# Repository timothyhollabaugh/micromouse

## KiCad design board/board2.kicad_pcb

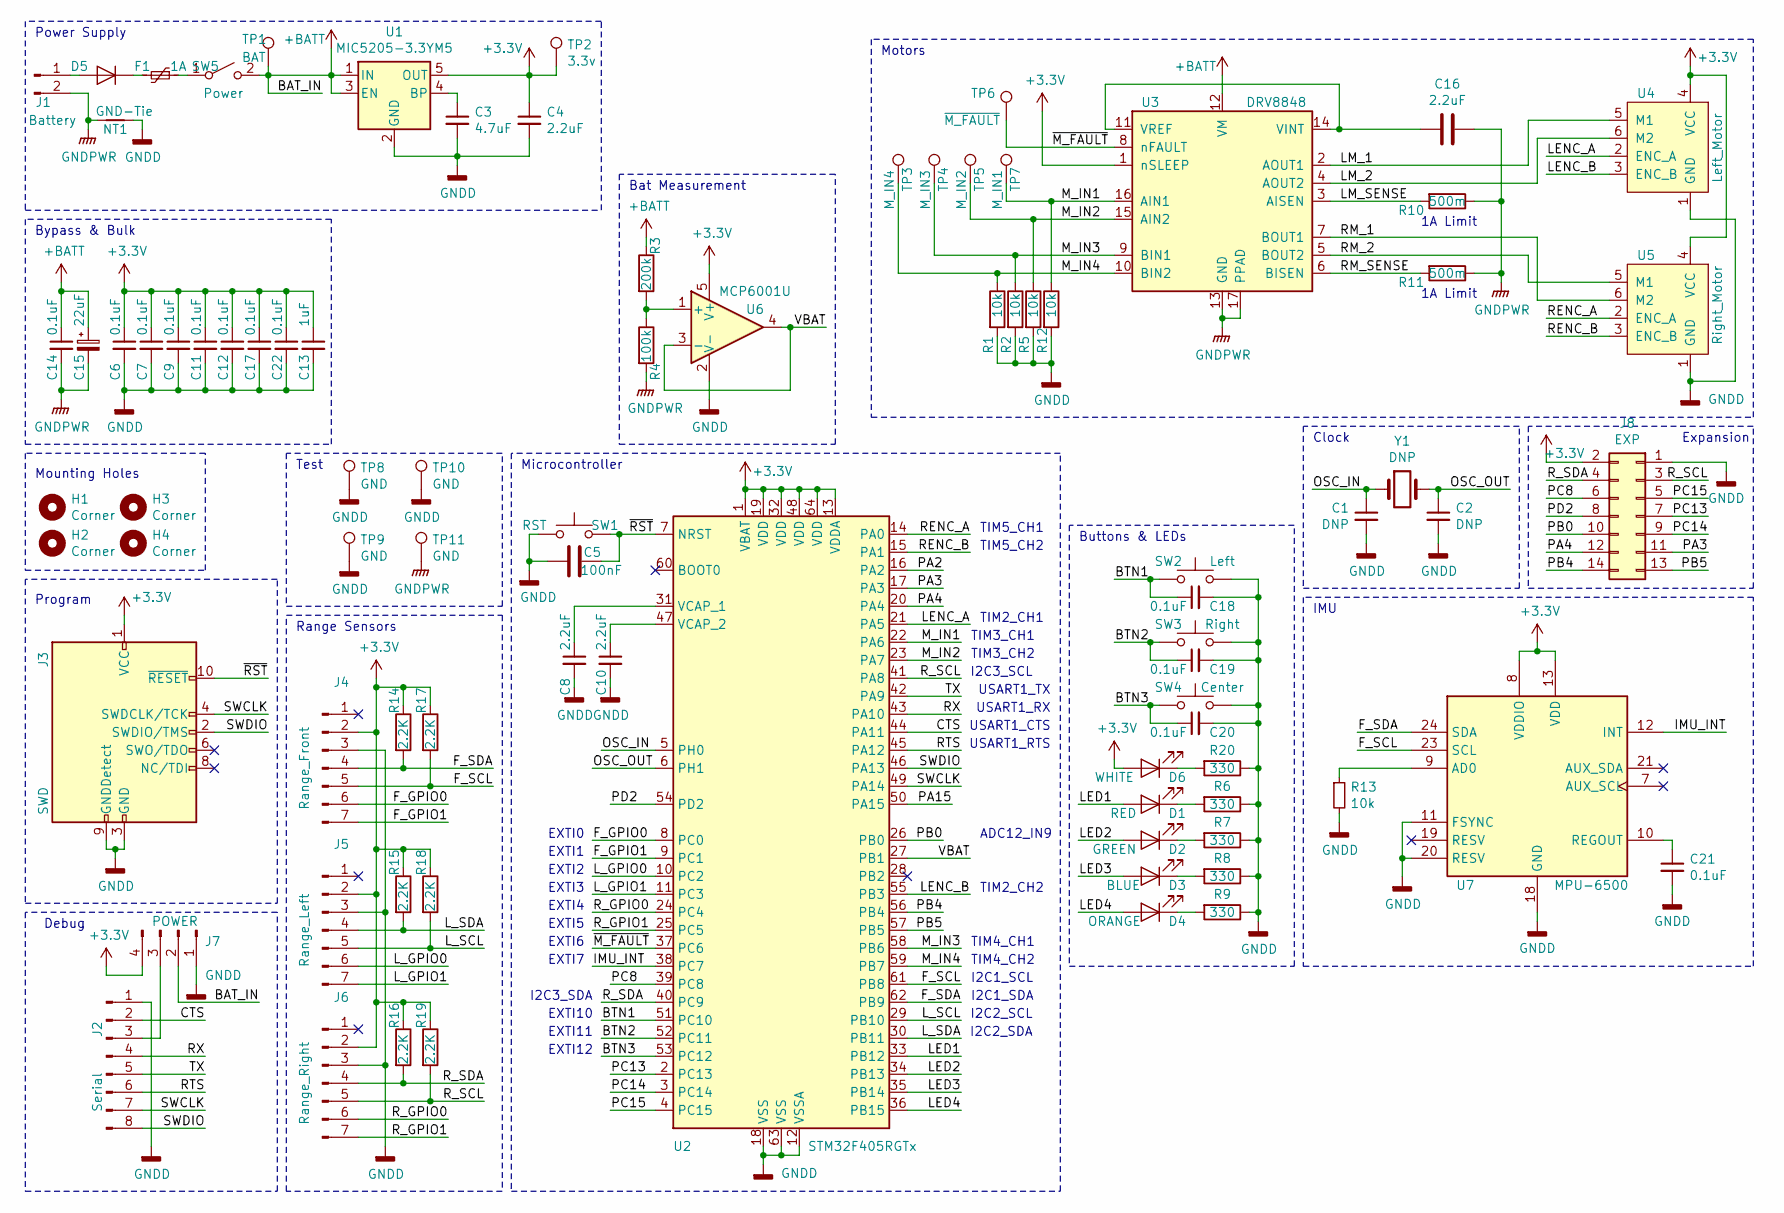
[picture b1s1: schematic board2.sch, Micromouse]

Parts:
C1, C2: DNP; C_0603_1608Metric
C3: 4.7uF; C_0603_1608Metric
C4, C8, C10, C16: 2.2uF; C_0603_1608Metric
C5: 100nF; C_0603_1608Metric
C6, C7, C9, C11, C12, C14, C17, C18, C19, C20, C21, C22: 0.1uF; C_0603_1608Metric
C13: 1uF; C_0603_1608Metric
C15: 22uF; CP_Elec_4x4.5
D1: RED; LED_0603_1608Metric
D2: GREEN; LED_0603_1608Metric
D3: BLUE; LED_0603_1608Metric
D4: ORANGE; LED_0603_1608Metric
D5: DB2441700L; SC-110A-2
D6: WHITE; LED_0603_1608Metric
F1: 1A; Littlefuse_154
H1, H2, H3, H4: Corner; MountingHole_2.2mm_M2
J1: Battery; PinHeader_1x02_P2.54mm_Horizontal
J2: Serial; PinHeader_1x08_P2.54mm_Vertical_SMD_Pin1Left
J3: SWD; PinHeader_2x05_P1.27mm_Vertical_SMD
J4: Range_Front; PinSocket_1x07_P2.54mm_Vertical
J5: Range_Left; PinSocket_1x07_P2.54mm_Vertical
J6: Range_Right; PinSocket_1x07_P2.54mm_Vertical
J7: POWER; PinHeader_1x04_P2.54mm_Vertical_SMD_Pin1Left
J8: EXP; PinHeader_2x07_P2.00mm_Vertical_SMD
NT1: GND-Tie; NetTie-2_SMD_Pad0.5mm
R1, R2, R5, R12, R13: 10k; R_0603_1608Metric
R3: 200k; R_0603_1608Metric
R4: 100k; R_0603_1608Metric
R6, R7, R8, R9, R20: 330; R_0603_1608Metric
R10, R11: 500m; R_1210_3225Metric
R14, R15, R16, R17, R18, R19: 2.2K; R_0603_1608Metric
SW1: RST; SW_SPST_PTS810
SW2: Left; SW_SPST_PTS810
SW3: Right; SW_SPST_PTS810
SW4: Center; SW_SPST_PTS810
SW5: Power; PinHeader_2x01_P2.54mm_Vertical_SMD
TP1: BAT; TestPoint_Pad_1.8x1.0mm
TP2: 3.3v; TestPoint_Pad_1.8x1.0mm
TP3: M_IN4; TestPoint_Pad_1.8x1.0mm
TP4: M_IN3; TestPoint_Pad_1.8x1.0mm
TP5: M_IN2; TestPoint_Pad_1.8x1.0mm
TP6: ~M_FAULT; TestPoint_Pad_1.8x1.0mm
TP7: M_IN1; TestPoint_Pad_1.8x1.0mm
TP8, TP9, TP10, TP11: GND; TestPoint_Pad_1.8x1.0mm
U1: MIC5205-3.3YM5; SOT-23-5
U2: STM32F405RGTx; LQFP-64_10x10mm_P0.5mm
U3: DRV8848; TSSOP-16_4.4x5mm_P0.65mm
U4: Left_Motor; Molex_PicoBlade_53261-0671_1x06-1MP_P1.25mm_Horizontal
U5: Right_Motor; Molex_PicoBlade_53261-0671_1x06-1MP_P1.25mm_Horizontal
U6: MCP6001U; SOT-23-5
U7: MPU-6500; InvenSense_QFN-24_4x4mm_P0.5mm
Y1: DNP; Crystal_SMD_0603-2Pin_6.0x3.5mm

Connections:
+3V3: C4.1, C6.1, C7.1, C9.1, C11.1, C12.1, C13.1, C17.1, C22.1, D6.2 (A), J3.1 (VCC), J4.2, J5.2, J6.2, J7.4, J8.2, R14.1, R15.1, R16.1, R17.1, R18.1, R19.1, TP2.1, U1.5 (OUT), U2.1 (VBAT), U2.13 (VDDA), U2.19 (VDD), U2.32 (VDD), U2.48 (VDD), U2.64 (VDD), U3.1 (nSLEEP), U4.4 (VCC), U5.4 (VCC), U6.5 (V+), U7.8 (VDDIO), U7.13 (VDD)
+BATT: C14.1, C15.1, J7.2, R3.1, SW5.2 (B), TP1.1, U1.1 (IN), U1.3 (EN), U3.12 (VM)
/BTN1: C18.1, SW2.1, U2.51 (PC10)
/BTN2: C19.1, SW3.1, U2.52 (PC11)
/BTN3: C20.1, SW4.1, U2.53 (PC12)
/CTS: J2.2, U2.44 (PA11)
/F_GPIO0: J4.6, U2.8 (PC0)
/F_GPIO1: J4.7, U2.9 (PC1)
/F_SCL: J4.5, R17.2, U2.61 (PB8), U7.23 (SCL)
/F_SDA: J4.4, R14.2, U2.62 (PB9), U7.24 (SDA)
/IMU_INT: U2.38 (PC7), U7.12 (INT)
/LED1: D1.2 (A), U2.33 (PB12)
/LED2: D2.2 (A), U2.34 (PB13)
/LED3: D3.2 (A), U2.35 (PB14)
/LED4: D4.2 (A), U2.36 (PB15)
/LENC_A: U2.21 (PA5), U4.2 (ENC_A)
/LENC_B: U2.55 (PB3), U4.3 (ENC_B)
/LM_1: U3.2 (AOUT1), U4.5 (M1)
/LM_2: U3.4 (AOUT2), U4.6 (M2)
/LM_SENSE: R10.2, U3.3 (AISEN)
/L_GPIO0: J5.6, U2.10 (PC2)
/L_GPIO1: J5.7, U2.11 (PC3)
/L_SCL: J5.5, R18.2, U2.29 (PB10)
/L_SDA: J5.4, R15.2, U2.30 (PB11)
/M_IN1: R12.1, TP7.1, U2.22 (PA6), U3.16 (AIN1)
/M_IN2: R5.1, TP5.1, U2.23 (PA7), U3.15 (AIN2)
/M_IN3: R2.1, TP4.1, U2.58 (PB6), U3.9 (BIN1)
/M_IN4: R1.1, TP3.1, U2.59 (PB7), U3.10 (BIN2)
/OSC_IN: C1.1, U2.5 (PH0), Y1.1
/OSC_OUT: C2.1, U2.6 (PH1), Y1.2
/PA3: J8.11, U2.17 (PA3)
/PA4: J8.12, U2.20 (PA4)
/PB0: J8.10, U2.26 (PB0)
/PB4: J8.14, U2.56 (PB4)
/PB5: J8.13, U2.57 (PB5)
/PC8: J8.6, U2.39 (PC8)
/PC13: J8.7, U2.2 (PC13)
/PC14: J8.9, U2.3 (PC14)
/PC15: J8.5, U2.4 (PC15)
/PD2: J8.8, U2.54 (PD2)
/RENC_A: U2.14 (PA0), U5.2 (ENC_A)
/RENC_B: U2.15 (PA1), U5.3 (ENC_B)
/RM_1: U3.7 (BOUT1), U5.6 (M2)
/RM_2: U3.5 (BOUT2), U5.5 (M1)
/RM_SENSE: R11.2, U3.6 (BISEN)
/RTS: J2.6, U2.45 (PA12)
/RX: J2.4, U2.43 (PA10)
/R_GPIO0: J6.6, U2.24 (PC4)
/R_GPIO1: J6.7, U2.25 (PC5)
/R_SCL: J6.5, J8.3, R19.2, U2.41 (PA8)
/R_SDA: J6.4, J8.4, R16.2, U2.40 (PC9)
/SWCLK: J2.7, J3.4 (SWDCLK/TCK), U2.49 (PA14)
/SWDIO: J2.8, J3.2 (SWDIO/TMS), U2.46 (PA13)
/TX: J2.5, U2.42 (PA9)
/VBAT: U2.27 (PB1), U6.3 (-), U6.4
/~M_FAULT: TP6.1, U2.37 (PC6), U3.8 (nFAULT)
/~RST: C5.1, J3.10 (~RESET~), SW1.2, U2.7 (NRST)
GNDD: C1.2, C2.2, C3.2, C4.2, C5.2, C6.2, C7.2, C8.2, C9.2, C10.2, C11.2, C12.2, C13.2, C17.2, C18.2, C19.2, C20.2, C21.2, C22.2, J2.1, J3.3 (GND), J3.5 (GND), J3.9 (GNDDetect), J4.3, J5.3, J6.3, J7.1, J8.1, NT1.2, R1.2, R2.2, R5.2, R6.1, R7.1, R8.1, R9.1, R12.2, R13.2, R20.1, SW1.1, SW2.2, SW3.2, SW4.2, TP8.1, TP9.1, TP10.1, U1.2 (GND), U2.12 (VSSA), U2.18 (VSS), U2.63 (VSS), U4.1 (GND), U5.1 (GND), U6.2 (V-), U7.11 (FSYNC), U7.18 (GND), U7.20 (RESV)
GNDPWR: C14.2, C15.2, C16.1, J1.2, NT1.1, R4.2, R10.1, R11.1, TP11.1, U3.13 (GND), U3.17 (PPAD)
unnamed: C3.1, U1.4 (BP)
unnamed: C8.1, U2.31 (VCAP_1)
unnamed: C10.1, U2.47 (VCAP_2)
unnamed: C16.2, U3.11 (VREF), U3.14 (VINT)
unnamed: C21.1, U7.10 (REGOUT)
unnamed: D1.1 (K), R6.2
unnamed: D2.1 (K), R7.2
unnamed: D3.1 (K), R8.2
unnamed: D4.1 (K), R9.2
unnamed: D5.1 (K), F1.2
unnamed: D5.2 (A), J1.1
unnamed: D6.1 (K), R20.2
unnamed: F1.1, SW5.1 (A)
unnamed: J2.3, J7.3
unnamed: R3.2, R4.1, U6.1 (+)
unnamed: R13.1, U7.9 (AD0)

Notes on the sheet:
TIM3_CH1
TIM3_CH2
TIM4_CH1
TIM4_CH2
TIM5_CH1
TIM5_CH2
TIM2_CH1
TIM2_CH2
I2C1_SCL
I2C1_SDA
I2C2_SCL
I2C2_SDA
I2C3_SCL
I2C3_SDA
EXTI0
EXTI1
EXTI2
EXTI3
EXTI4
EXTI5
EXTI6
USART1_TX
USART1_RX
USART1_CTS
USART1_RTS
EXTI10
EXTI11
EXTI12
ADC12_IN9
EXTI7
Range Sensors
IMU
Microcontroller
Buttons & LEDs
Expansion
Clock
Program
Debug
Test
Power Supply

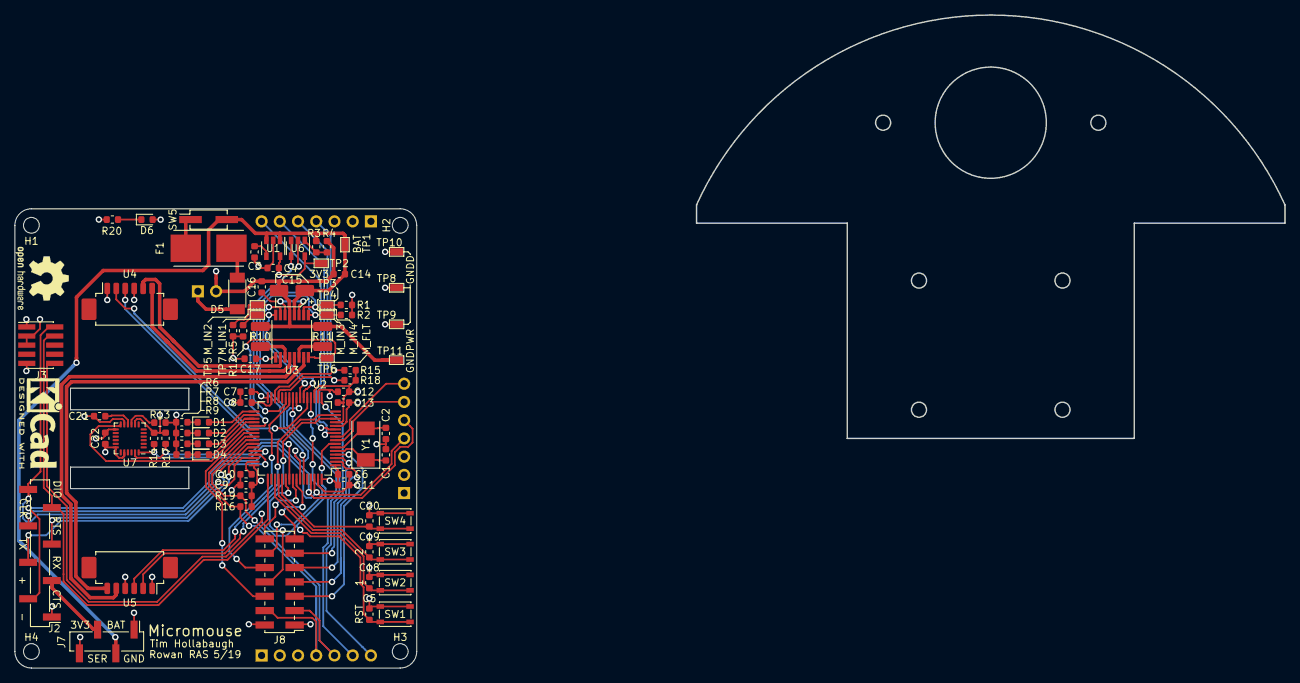
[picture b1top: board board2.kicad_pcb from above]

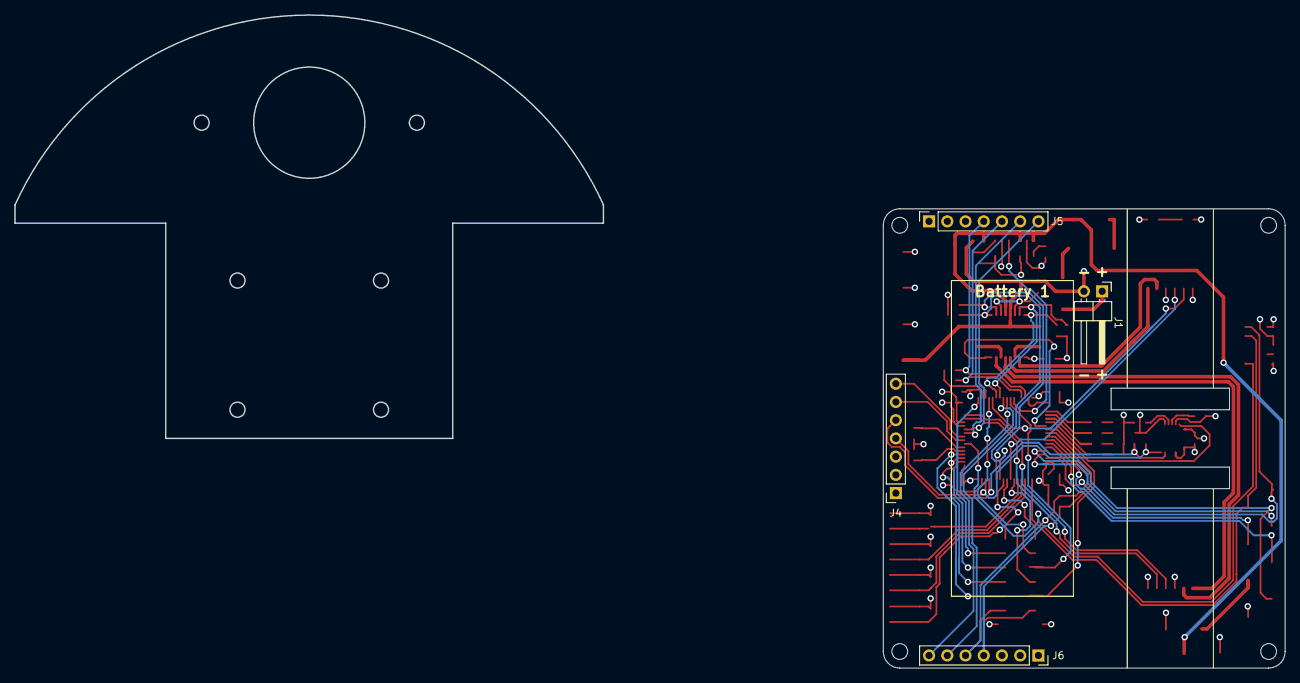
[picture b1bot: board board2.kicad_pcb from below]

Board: 4 copper layers, 177.0 x 91.0 mm, 86 parts (4 on the bottom side), 75 nets.

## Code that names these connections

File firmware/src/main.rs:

#![no_std]
#![no_main]

/**
 *
 * Important mechanical parameters:
 *
 *  - wheel diameter: 32mm
 *  - wheel circumference: 100mm
 *  - gear raitio: 75:1
 *  - counts per motor rev: 12
 *  - counts per wheel rev: 900
 *  - counts per mm: 9
 *  - wheelbase diameter: 73mm
 *  - wheelbase circumference: 229.336mm
 *  - ticks per spin: 2064.03
 *
 *  Positive spin is clockwise (right)
 *  Positive linear is forward
 *
 */
// pick a panicking behavior
// you can put a breakpoint on `rust_begin_unwind` to catch panics
extern crate panic_halt;

pub mod battery;
pub mod motors;
pub mod time;
pub mod uart;
pub mod vl6180x;

use core::fmt::Write;
use cortex_m_rt::entry;
use cortex_m_rt::exception;
use cortex_m_rt::ExceptionFrame;
use stm32f4xx_hal as stm32f4;
use stm32f4xx_hal::prelude::*;
use stm32f4xx_hal::stm32 as stm32f405;

use serde::Serialize;

use heapless::Vec;

use postcard;

use typenum::consts::U1024;

use mouse::comms::DebugMsg;
use mouse::comms::DebugPacket;
#[allow(unused_imports)]
use mouse::config::*;
use mouse::map::Direction;
use mouse::map::Orientation;
use mouse::map::Vector;
use mouse::mouse::Mouse;
use mouse::mouse::MouseConfig;
use mouse::mouse::MouseDebug;

use crate::battery::Battery;
use crate::time::Time;

use crate::uart::Uart;

use crate::motors::{Encoder, Motor};

use crate::motors::left::{LeftEncoder, LeftMotor};
use crate::motors::right::{RightEncoder, RightMotor};

// Setup the master clock out
pub fn mco2_setup(rcc: &stm32f405::RCC, gpioc: &stm32f405::GPIOC) {
    rcc.ahb1enr.write(|w| w.gpiocen().set_bit());
    rcc.cfgr.modify(|_, w| w.mco2().sysclk());
    gpioc.moder.write(|w| w.moder9().alternate());
    gpioc.afrh.write(|w| w.afrh9().af0());
}

#[entry]
fn main() -> ! {
    let p = stm32f4::stm32::Peripherals::take().unwrap();
    let _cp = stm32f405::CorePeripherals::take().unwrap();

    // Init non-hal things
    let mut time = Time::setup(&p.RCC, p.TIM1);

    while time.now() < 10000 {}

    let mut battery = Battery::setup(&p.RCC, &p.GPIOB, p.ADC1);

    let mut uart = Uart::setup(&p.RCC, p.USART1, &p.GPIOA);

    let mut left_motor = LeftMotor::setup(&p.RCC, p.TIM3, &p.GPIOA);
    let left_encoder = LeftEncoder::setup(&p.RCC, &p.GPIOA, &p.GPIOB, p.TIM2);

    let mut right_motor = RightMotor::setup(&p.RCC, p.TIM4, &p.GPIOB);
    let right_encoder = RightEncoder::setup(&p.RCC, &p.GPIOA, p.TIM5);

    // Init the hal things
    let rcc = p.RCC.constrain();
    let clocks = rcc.cfgr.freeze();

    let gpioa = p.GPIOA.split();
    let gpiob = p.GPIOB.split();
    let gpioc = p.GPIOC.split();

    let mut red_led = gpiob.pb12.into_push_pull_output();
    let mut green_led = gpiob.pb13.into_push_pull_output();
    let mut blue_led = gpiob.pb14.into_push_pull_output();
    let mut orange_led = gpiob.pb15.into_push_pull_output();

    let left_button = gpioc.pc10.into_pull_up_input();
    let _middle_button = gpioc.pc11.into_pull_up_input();
    let right_button = gpioc.pc12.into_pull_up_input();

    orange_led.set_high().ok();
    blue_led.set_low().ok();

    uart.add_bytes(b"Initializing\n").ok();

    let mut front_distance = {
        let scl = gpiob.pb8.into_open_drain_output().into_alternate_af4();
        let sda = gpiob.pb9.into_open_drain_output().into_alternate_af4();

        let mut gpio0 = gpioc.pc0.into_open_drain_output();
        gpio0.set_high().ok();

        let mut gpio1 = gpioc.pc1.into_open_drain_output();
        gpio1.set_high().ok();

        let i2c =
            stm32f4::i2c::I2c::i2c1(p.I2C1, (scl, sda), 100.khz(), clocks);

        time.delay(10000);

        let mut distance = vl6180x::VL6180x::new(i2c, 0x29);
        distance.init_private_registers();
        distance.init_default();
        distance
    };

    orange_led.set_low().ok();
    blue_led.set_high().ok();

    let mut left_distance = {
        let scl = gpiob.pb10.into_open_drain_output().into_alternate_af4();
        let sda = gpiob.pb11.into_open_drain_output().into_alternate_af4();

        let mut gpio0 = gpioc.pc2.into_open_drain_output();
        gpio0.set_high().ok();

        let mut gpio1 = gpioc.pc3.into_open_drain_output();
        gpio1.set_high().ok();

        let i2c =
            stm32f4::i2c::I2c::i2c2(p.I2C2, (scl, sda), 100.khz(), clocks);

        time.delay(1000);

        let mut distance = vl6180x::VL6180x::new(i2c, 0x29);
        distance.init_private_registers();
        distance.init_default();
        distance
    };

    orange_led.set_high().ok();
    blue_led.set_high().ok();

    let mut right_distance = {
        let scl = gpioa.pa8.into_open_drain_output().into_alternate_af4();
        let sda = gpioc.pc9.into_open_drain_output().into_alternate_af4();

        let mut gpio0 = gpioc.pc4.into_open_drain_output();
        gpio0.set_high().ok();

        let mut gpio1 = gpioc.pc5.into_open_drain_output();
        gpio1.set_high().ok();

        let i2c =
            stm32f4::i2c::I2c::i2c3(p.I2C3, (scl, sda), 100.khz(), clocks);

        time.delay(1000);

        let mut distance = vl6180x::VL6180x::new(i2c, 0x29);
        distance.init_private_registers();
        distance.init_default();
        distance
    };

    blue_led.set_low().ok();
    orange_led.set_low().ok();

    let config = MouseConfig {
        mechanical: MOUSE_2019_MECH,
        path: MOUSE_2019_PATH,
        map: MOUSE_MAZE_MAP,
        motion: MOUSE_2019_MOTION,
    };

    let initial_orientation = Orientation {
        position: Vector {
            x: 1250.0,
            y: 1350.0,
        },
        direction: Direction::from(0.0),
    };

    uart.add_bytes(b"\n\nstart").ok();

    let mut last_time: u32 = time.now();

    let mut mouse = Mouse::new(
        &config,
        initial_orientation,
        last_time,
        left_encoder.count(),
        right_encoder.count(),
    );

    front_distance.start_ranging();
    left_distance.start_ranging();
    right_distance.start_ranging();

    let mut running = false;
    let mut debugging = false;

    let mut packet_count = 0;
    let mut step_count = 0;

    loop {
        let now: u32 = time.now();

        front_distance.update();
        right_distance.update();
        left_distance.update();

        if let Ok(byte) = uart.read_byte() {
            match byte {
                0 => {}
                1 => debugging = false,
                2 => debugging = true,
                3 => running = false,
                4 => running = true,
                _ => {}
            }
        }

        if now - last_time >= 10 {
            green_led.toggle().ok();

            if running {
                let left_encoder_count = left_encoder.count();
                let right_encoder_count = right_encoder.count();
                let left_distance_range = left_distance.range();
                let front_distance_range = front_distance.range();
                let right_distance_range = right_distance.range();

                let (left_power, right_power, debug) = mouse.update(
                    &config,
                    now,
                    battery.raw(),
                    left_encoder_count,
                    right_encoder_count,
                    left_distance_range,
                    front_distance_range,
                    right_distance_range,
                );

                right_motor.change_power((right_power * 10000.0 / 6.0) as i32);
                left_motor.change_power((left_power * 10000.0 / 6.0) as i32);

                if debugging && uart.tx_len() == Ok(0) {
                    let mut msgs = Vec::new();
                    msgs.push(DebugMsg::Orientation(debug.orientation.clone()));
                    msgs.push(DebugMsg::Motion(debug.motion.clone()));

                    //if step_count % 2 == 0 {
                    msgs.push(DebugMsg::Path(debug.path.clone()));
                    //}

                    let packet = DebugPacket {
                        msgs,
                        battery: debug.battery,
                        time: debug.time,
                        count: packet_count,
                    };

                    if let Ok(bytes) = postcard::to_vec::<U1024, _>(&packet) {
                        uart.add_bytes(&bytes);
                        orange_led.toggle().ok();
                    }

                    packet_count += 1;
                }

                step_count += 1;
            } else {
                right_motor.change_power(0);
                left_motor.change_power(0);
            }

            if left_button.is_low().unwrap() {
                running = true;
            }

            if right_button.is_low().unwrap() {
                running = false;
            }

            if battery.is_dead() {
                red_led.set_high().ok();
            } else {
                red_led.set_low().ok();
            }

            last_time = now;
        }

        battery.update(now);
    }
}

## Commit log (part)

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2019-10-04 Remove embedded examples
2019-10-04 Remove JetBrains .idea
2019-10-04 Move logic to mouse lib
2019-10-04 Add some calcs to the dataflow
2019-10-05 Add mapping module to keep track of location
2019-10-05 Mouse::new so mice can be created
2019-10-05 Add debug structs for debugging
2019-10-05 Save old encoders and time
2019-10-05 Up the max speed
2019-10-06 Arcs!
2019-10-06 Got in circles, tune PID
2019-10-07 Add left turns to the path
2019-10-07 Put simulation in charge of timing
2019-10-07 Decouple simulation running from updating gui
2019-10-13 Function for rect paths, upload scripts
2019-10-13 Switch angles so positive is CCW
2019-10-21 Schematic from older board
2019-10-21 Add test mouse for testing
2019-10-22 Calculate target direction to get back to center, then do pid on that
    Also add Direction type to handle wrapping at 2pi
2019-10-27 Separate configs
2019-10-27 Print debug with constant formating
2019-10-27 Buffer lines better
2019-11-08 Calc target angle, then PID on that angle instead of PID on the distance
    Helps make sure it is facing the right direction when close to the path
2019-11-10 Config for 2020 mouse
2019-11-10 Plot angles
2019-11-10 Ignore temp .dat files
2019-11-10 Poster
2019-11-11 Remove unused files
2019-11-12 Fix warnings
2019-11-13 Add config for 2020 mouse with old wheels
2019-11-13 Change test rectangle to have larger radius
    Avoid large accelerations when turning
    If radius = width/2, there is a segment of 0 length and gets a NaN
2019-11-16 Take distances into mouse and map
2019-11-16 Index edges in a maze and something for projecting onto walls
    Should allow getting what wall is being looked at
2019-11-17 Draw the maze
2019-11-18 Include perimeter in edge index
2019-11-18 Figure out which wall is being looked at
2019-11-22 Make wall projection into iterator so walls past the first can be found
2019-11-23 Save all the mouse states
2019-11-23 Split simulation into gui and simulation threads
    Helps performance a lot on Windows
2019-11-23 Find the left and right walls as well
2019-11-29 Attempt to limit power changes to wheels to avoid slipping
2019-12-19 WIP conrod UI
2019-12-20 Draw the mice
2019-12-20 Highlight the walls the mouse sees
2019-12-21 Add serde to everything
2019-12-22 Compile to wasm and use JS as simulation UI
2019-12-22 Put config in debug, actually use real config in update
2019-12-22 UI that shows blank maze
2019-12-22 Draw the mice and maze from debug
2019-12-23 Debug tree viewer for all the debug values
2019-12-23 Reset button
2019-12-24 Keep history of debugs
    Allows stepping through it
    Also some helper functions for building a UI
2019-12-24 Move start and reset buttons to left
2019-12-24 Plot a hardcoded value
2019-12-25 Graph shows current index and zero
2019-12-25 Can choose the y range of the graphs
2019-12-25 Recheck the graph checks when a node is reopened
2019-12-25 Can adjust min/max on graphs
2019-12-28 Send debug from mouse in postcard format
2019-12-28 Add simulation js libs
2019-12-29 Allow setting config through UI
2019-12-29 Periodically send some of the debug data
2019-12-29 Send time of debug, not time of sending
2020-01-01 Put the UI in cards
2020-01-01 Use port 3030 for openocd to not conflict with things that want 3333
2020-01-01 Start openocd before upload in upload.sh
2020-01-01 Start remote mouse support for UI
2020-01-01 Favicon
2020-01-01 Get remote mouse data through properly
2020-01-01 Split up ui into several files
2020-01-01 Comms error handling
2020-01-02 Draw path on maze
2020-01-02 History control works again
2020-01-03 Factor out card ui to function
2020-01-03 Better state control
2020-01-03 Don't enable/disable on every update
    Performance
2020-01-03 Make the maze not upside down
2020-01-03 Simpler delta power limiting that limits power per wheel
2020-01-05 Script to build the wasm
    Needs wasm-pack
    cargo install wasm-pack
2020-01-05 Reset UI if debug comes in with lower time than latest debug
2020-01-05 Clamp wheel power in simulation
2020-01-05 Show target direction on maze
2020-01-05 Redo motion handling.
    Now controlled by linear power and ratio of angular power / linear power. This keeps it turning at the same radius if the power changes. Also limits change in power to wheels, and attempts to clamp w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
2020-01-05 Start retuning for new motion control
2020-01-05 Start real mouse where the path starts
2020-01-05 Report battery level and path and motion
2020-01-05 Do circles for testing
2020-01-05 Tune for 2019 mouse on a bench
2020-01-07 Switch to 2020 mouse config
2020-01-07 Do an oval for testing
2020-01-07 Up baud to 230400
2020-01-07 Run wasm init function to set panic handler
2020-01-08 Create cargo workspace for all the crates
2020-01-08 Rename crates to be more consistent
2020-01-08 Add motor characterization function
    Steps through motor powers and reports encoder ticks, battery level
2020-01-08 Remove unsused crate from workspace config
2020-01-09 Lighten the unknown wall color
2020-01-10 Follow a line for tuning
2020-01-10 More tuning
2020-01-10 Remove unused .cargo-ok
2020-01-11 Use bezier curves
    Also factor out some vector math and add tests
    Also temporarily remove config menu from ui
    Also use default config from config.rs instead of duplicating in the ui
2020-01-11 Remove old penplot
2020-01-13 Redo a lot of the path definitions
    Now implement beziers ourselves, since libs use std
    Beziers and other curves now in bezier.rs and impl Curve trait for standard interface
    (will probably use only beziers though)
    Now Segment struct to hide impl details of which curve type is used
    Closest point calculation happens in path update, gets added to debug and shown on UI
    Vector, Direction, Orientation moved to new math.rs since they are used a lot outside mapping
2020-01-19 Better upload scripts, fix warning, some tuning
2020-01-19 Do PIDF on the curvature
2020-01-22 Put offset curvature in it's own function
2020-01-24 Make sure offset_curvature works for zero curvature
2020-01-27 Do PID on encoder ticks / ms instead if mm / ms for more resolution and tune for 2019 mouse
2020-01-30 Do PID on curvature
2020-01-31 Tune the simulation
2020-02-01 Project onto maze
2020-02-01 Project onto maze in order?
2020-02-01 Remove nodes from debug tree when they go away
2020-02-01 Iterate maze projections in the right order
2020-02-01 Project left and right sensors
2020-02-12 Rename find_closest_walls to find_closest_wall
2020-02-12 Maze projection also returns hit point and distance
2020-02-12 Use a new WallDirection instead of horizontal: bool to make it more clear
2020-02-14 Show hitpoints and zoom map
2020-02-14 Fix wheel slip simulation
2020-02-15 Account for 2 possible positions when localizing
2020-02-15 Update simulation state after generating debug info
    Keeps the simulation debug in sync with the mouse debug
2020-02-15 If the approx direction from approx sensor orientation does not help in determining which direction to use, use an approx direction based on the previous location.
2020-02-15 Put the correct delta position in the debug
2020-02-15 Only show projected walls if they are there, change uart baud.
2020-02-17 Drop baud to 115200 for wifi
2020-02-17 Add hardware inputs to debug
    Includes encoders and distance sensors
2020-02-17 Filter the distance readings
    Averages them over 8 samples
2020-02-18 Don't calc direction from sensors
    It is very noisy and makes things break.
2020-02-19 Up sim wheel accel
2020-02-19 Hardware readouts
2020-02-19 Don't draw the maze if it isn't in the debug info
2020-02-19 Use 5th order beziers
    Smoother curves when r=90
2020-02-21 Fix filter
2020-02-21 Only use distances if angle is within pi/8
2020-02-21 Account for when only one side wall is seen
2020-02-22 Rip out the localization and put in a simpler version
2020-02-22 Fix timer overflow from when the clock was increased
2020-02-22 Filter the distance sensors
2020-02-23 Follows a path pretty well
2020-02-24 Up the dead battery level
2020-02-24 Split localization and mapping. Add basic mapping.
2020-02-29 Reorganized everything, added navigation, and turns.
2020-02-29 Fix it up for maze use
    Only send debugs if starting or started
    React to UART bytes correctly
    Function to echo UART
2020-03-01 If about to hit wall, don't
    Doesn't always work
    Also fix some uturn bugs
2020-03-01 Include actual maze
2020-03-01 Draw maze cells
2020-03-01 Motion plan end position west case should offset in x direction
2020-03-01 off-by-one when drawing maze
2020-03-01 use sensors
2020-03-02 Slow down turning
2020-03-02 Shrink the motion buffer
2020-03-03 Improvements for real life
2020-03-03 Increase front tolerance
2020-03-04 Adjust sensor thresholds
2020-03-04 Show up to cell count of 32 instead of 10
2020-03-04 Don't go to center of cell when uturning
2020-03-08 Handle debug values being null
2020-03-08 Make sure delta^2 of last side sensors is within limits
2020-03-18 Start schematic
2020-04-17 Gitlab ci to run tests
2020-04-17 Fix a failing motion planning test
2020-04-17 Include flow png, test cache
2020-04-17 build ci
2020-04-17 Install build deps in ci
2020-04-18 Fix typo
2020-04-18 Download pre-compiled wasm-pack
2020-04-18 Cache per job
2020-04-18 Only run pages on master
2020-04-21 System test to allow uart control of hardware
2020-04-22 analysis: calculate motor velocities
2020-04-22 analysis: graph motor velocity and position
2020-04-22 analysis: Calculate 1st order transfer function
2020-04-22 analysis: fix time offset
2020-04-22 firmware: send report every 1ms when in system test
2020-04-22 analysis: make lines thinner
2020-04-22 analysis: step multiple times and take average
2020-04-23 analysis: recover when numbers could not be parsed
2020-04-23 analysis: Allow changing gain when stepping motors
2020-04-25 analysis: Put motor analysis main code in a function and only call it if the modules is run
2020-04-25 analysis: Plot averaged step response all the way to the end
2020-04-26 analysis: Plot system
2020-04-28 analysis: Attempt to run a frequency response
2020-04-28 simulator: Run simulation during CI
2020-04-28 ci: hopefully cache better
2020-04-28 simulator: run_sim outputs in gitlab metrics format
2020-04-28 ci: whereis cargo?
2020-04-28 ci: use correct cargo home
2020-04-28 ci: remove cache for now
2020-04-28 ci: Adjust metrics path
2020-05-06 analysis: Add script to calculate required motor accelerations
2020-05-09 firmware: Option to report distance sensors in system test
2020-05-09 analysis: Add delay to the system
2020-05-09 logic: Offset turn moves correctly when motion planning
2020-05-10 logic: localize: Only filter the distances if they are going to be used
2020-05-10 logic: change sim config turn tolerance to match real mice
2020-05-10 logic: localize: Filter distance by max range and us the last reading when the current is unknown
2020-05-10 logic: map: reset saved readings once they are all there
2020-05-10 logic: localize: Make sure both left and right sensors are reading to use them
2020-05-10 logic: localize: Front sensor offset from the cell that the front sensor is in
    Had issues before when the mouse and the sensor were in different cells, caused a cell jump.
2020-05-10 logic: localize: Don't reset last raw distance in filter when not stabilized
2020-05-11 logic: config: Reverse wheels for other board
2020-05-11 logic: motion_plan: Make the center manual turn range smaller
2020-05-11 logic: localize: fix filter tests
2020-05-12 logic: map: map the maze
2020-05-12 simulation: go through history when scrolling the step box
2020-05-12 simulation: Don't throw errors if slow does not exist in debug
2020-05-12 simulation: run_sim: Maze file names are passed on command line
2020-05-14 firmware: report maze (hardfaults)
2020-05-15 firmware: cleanup
